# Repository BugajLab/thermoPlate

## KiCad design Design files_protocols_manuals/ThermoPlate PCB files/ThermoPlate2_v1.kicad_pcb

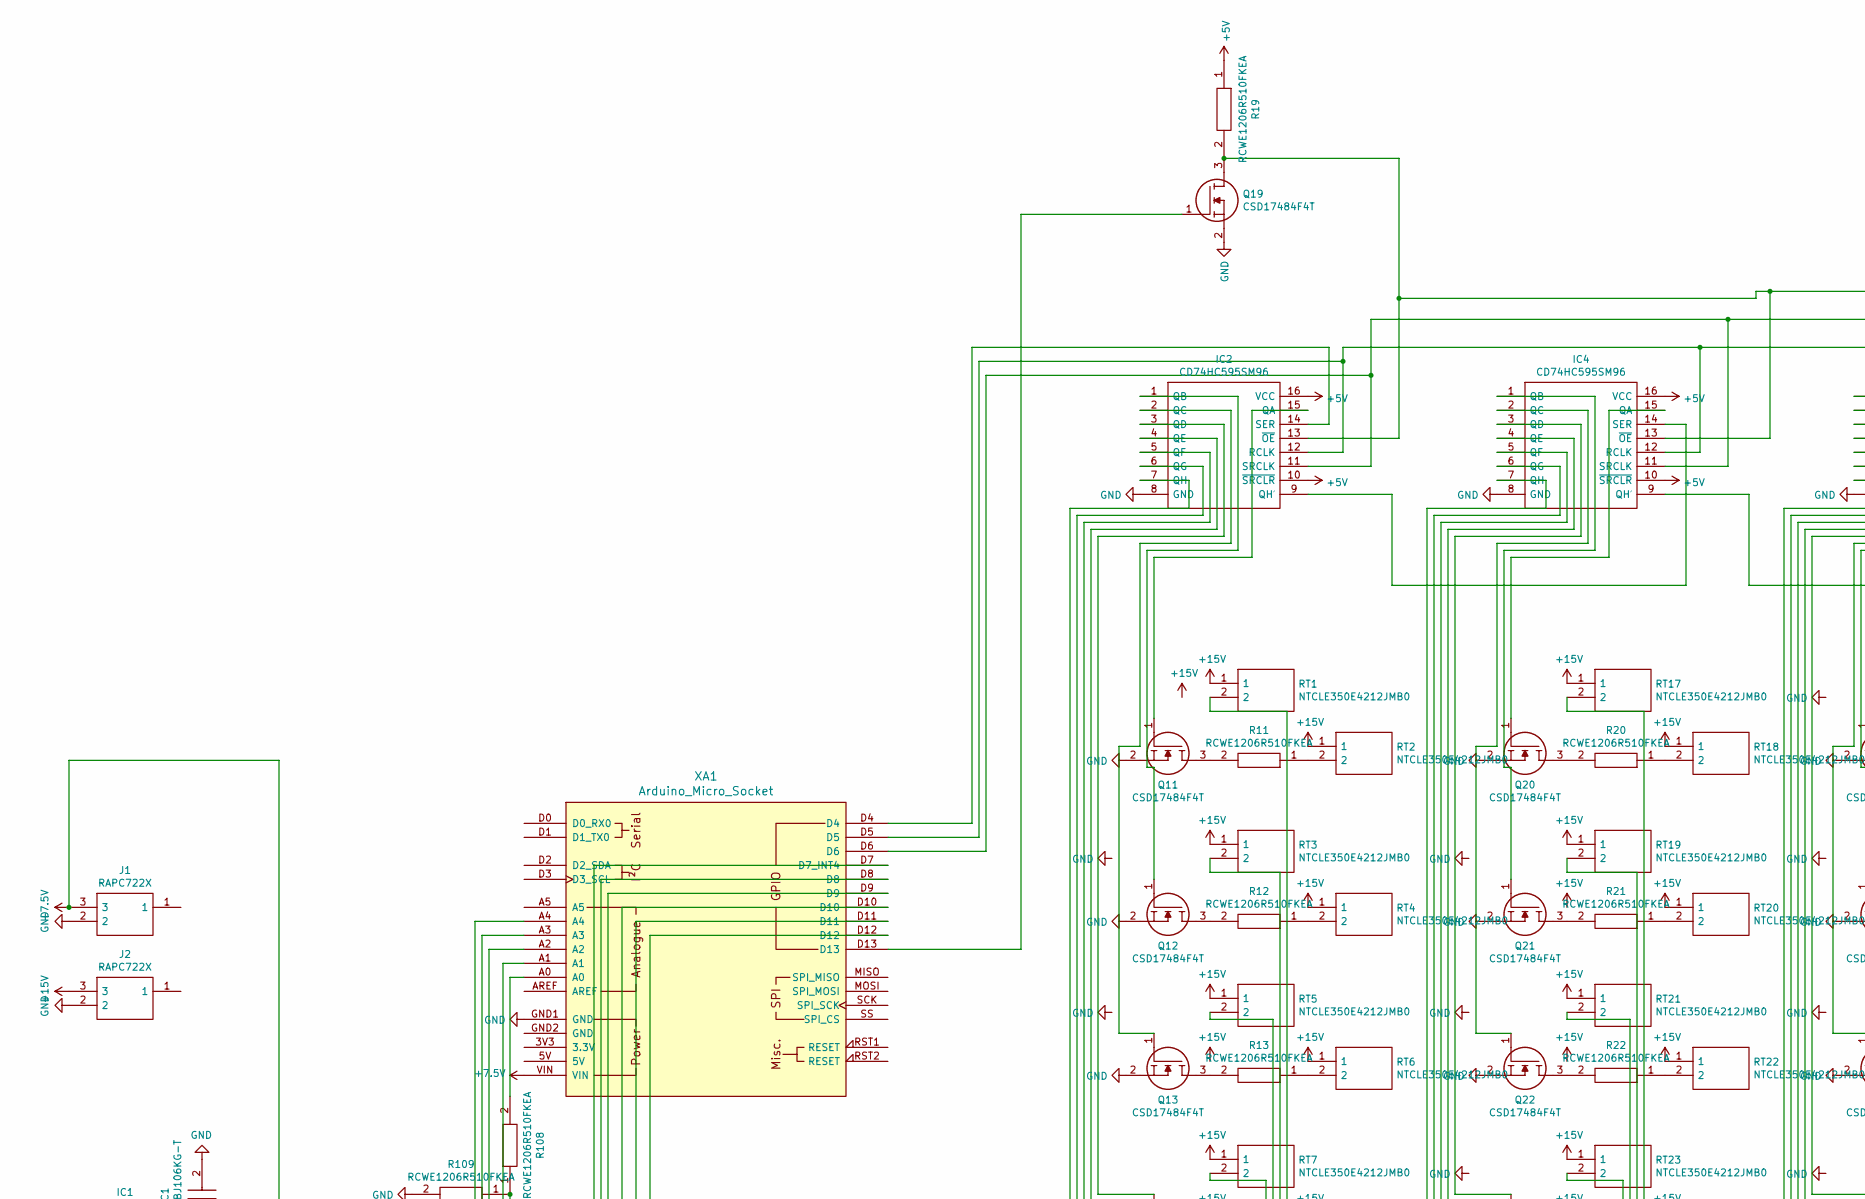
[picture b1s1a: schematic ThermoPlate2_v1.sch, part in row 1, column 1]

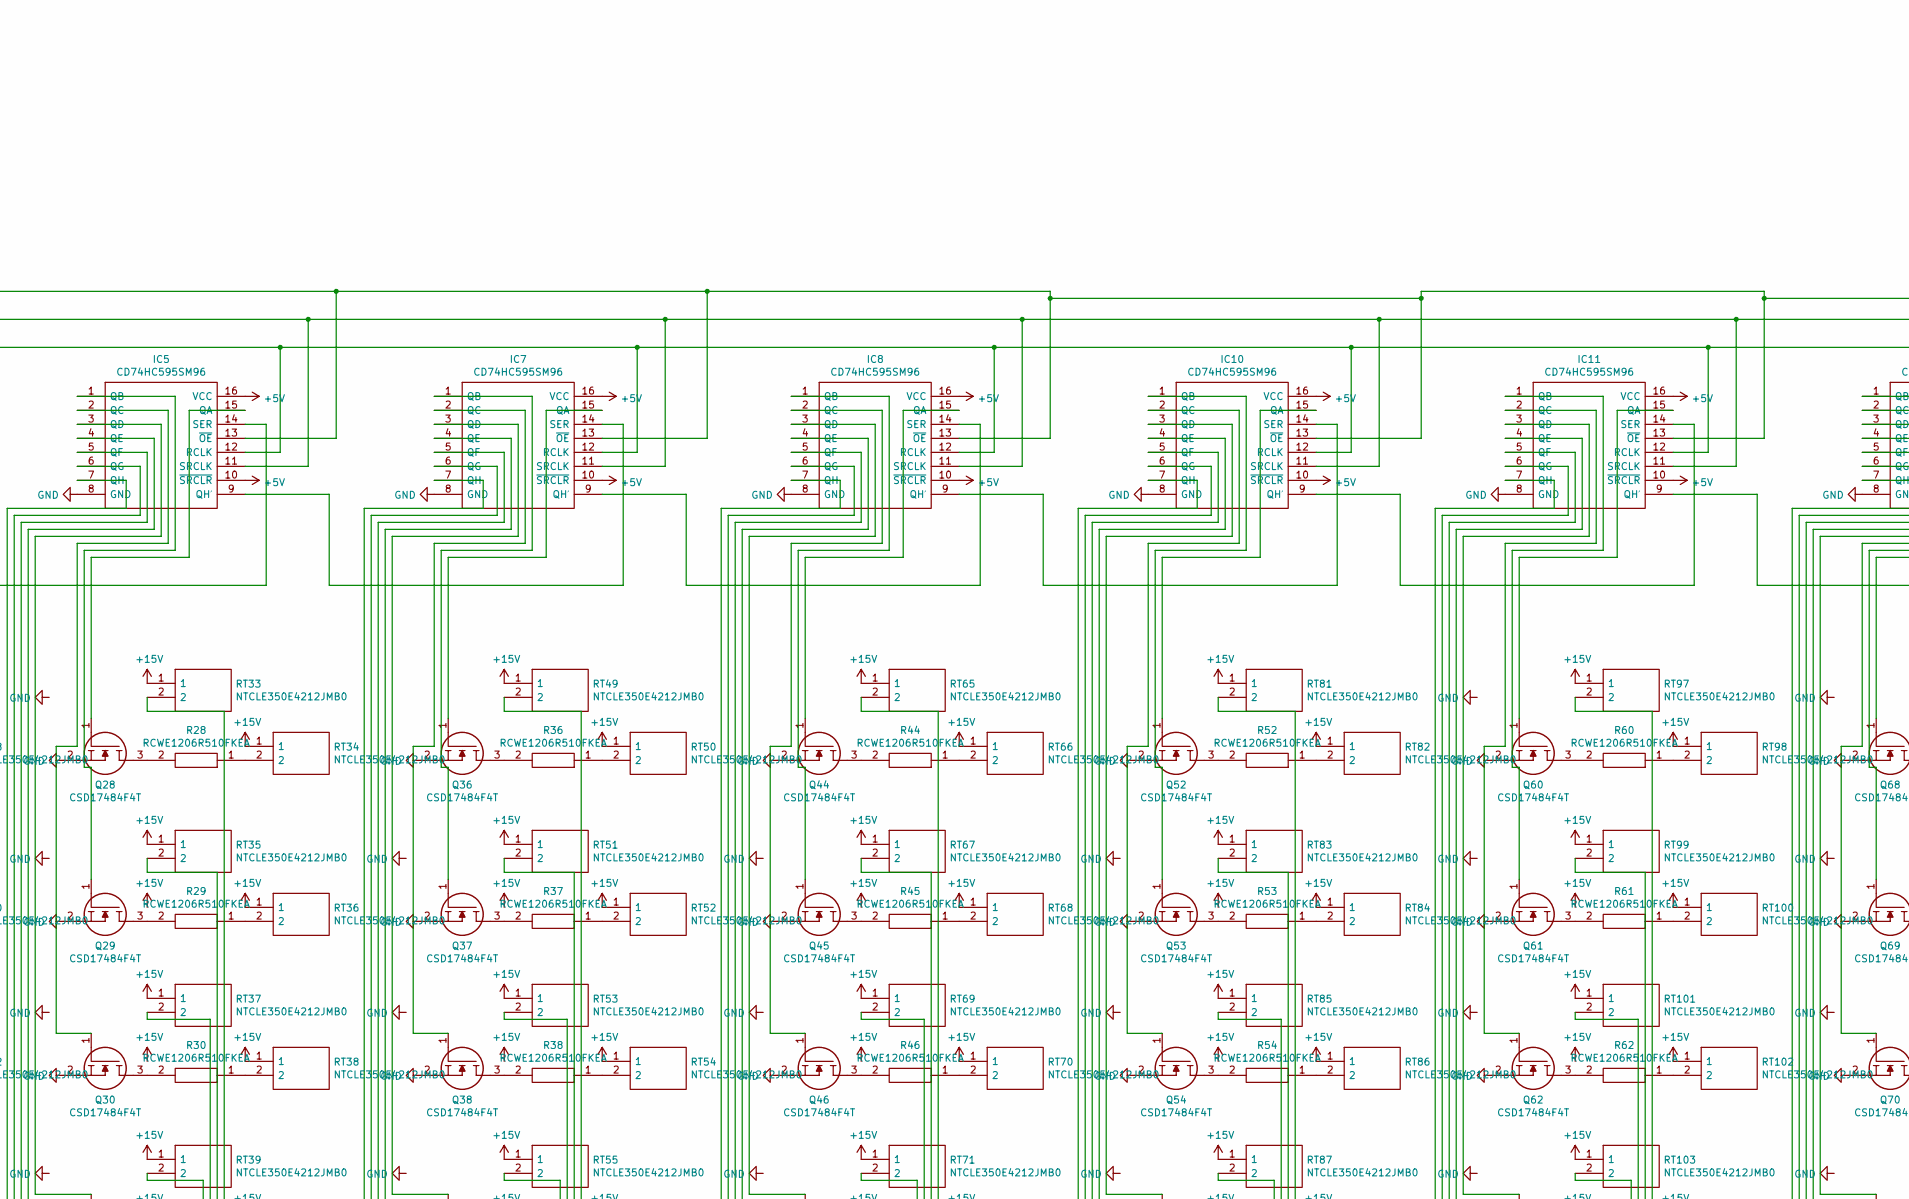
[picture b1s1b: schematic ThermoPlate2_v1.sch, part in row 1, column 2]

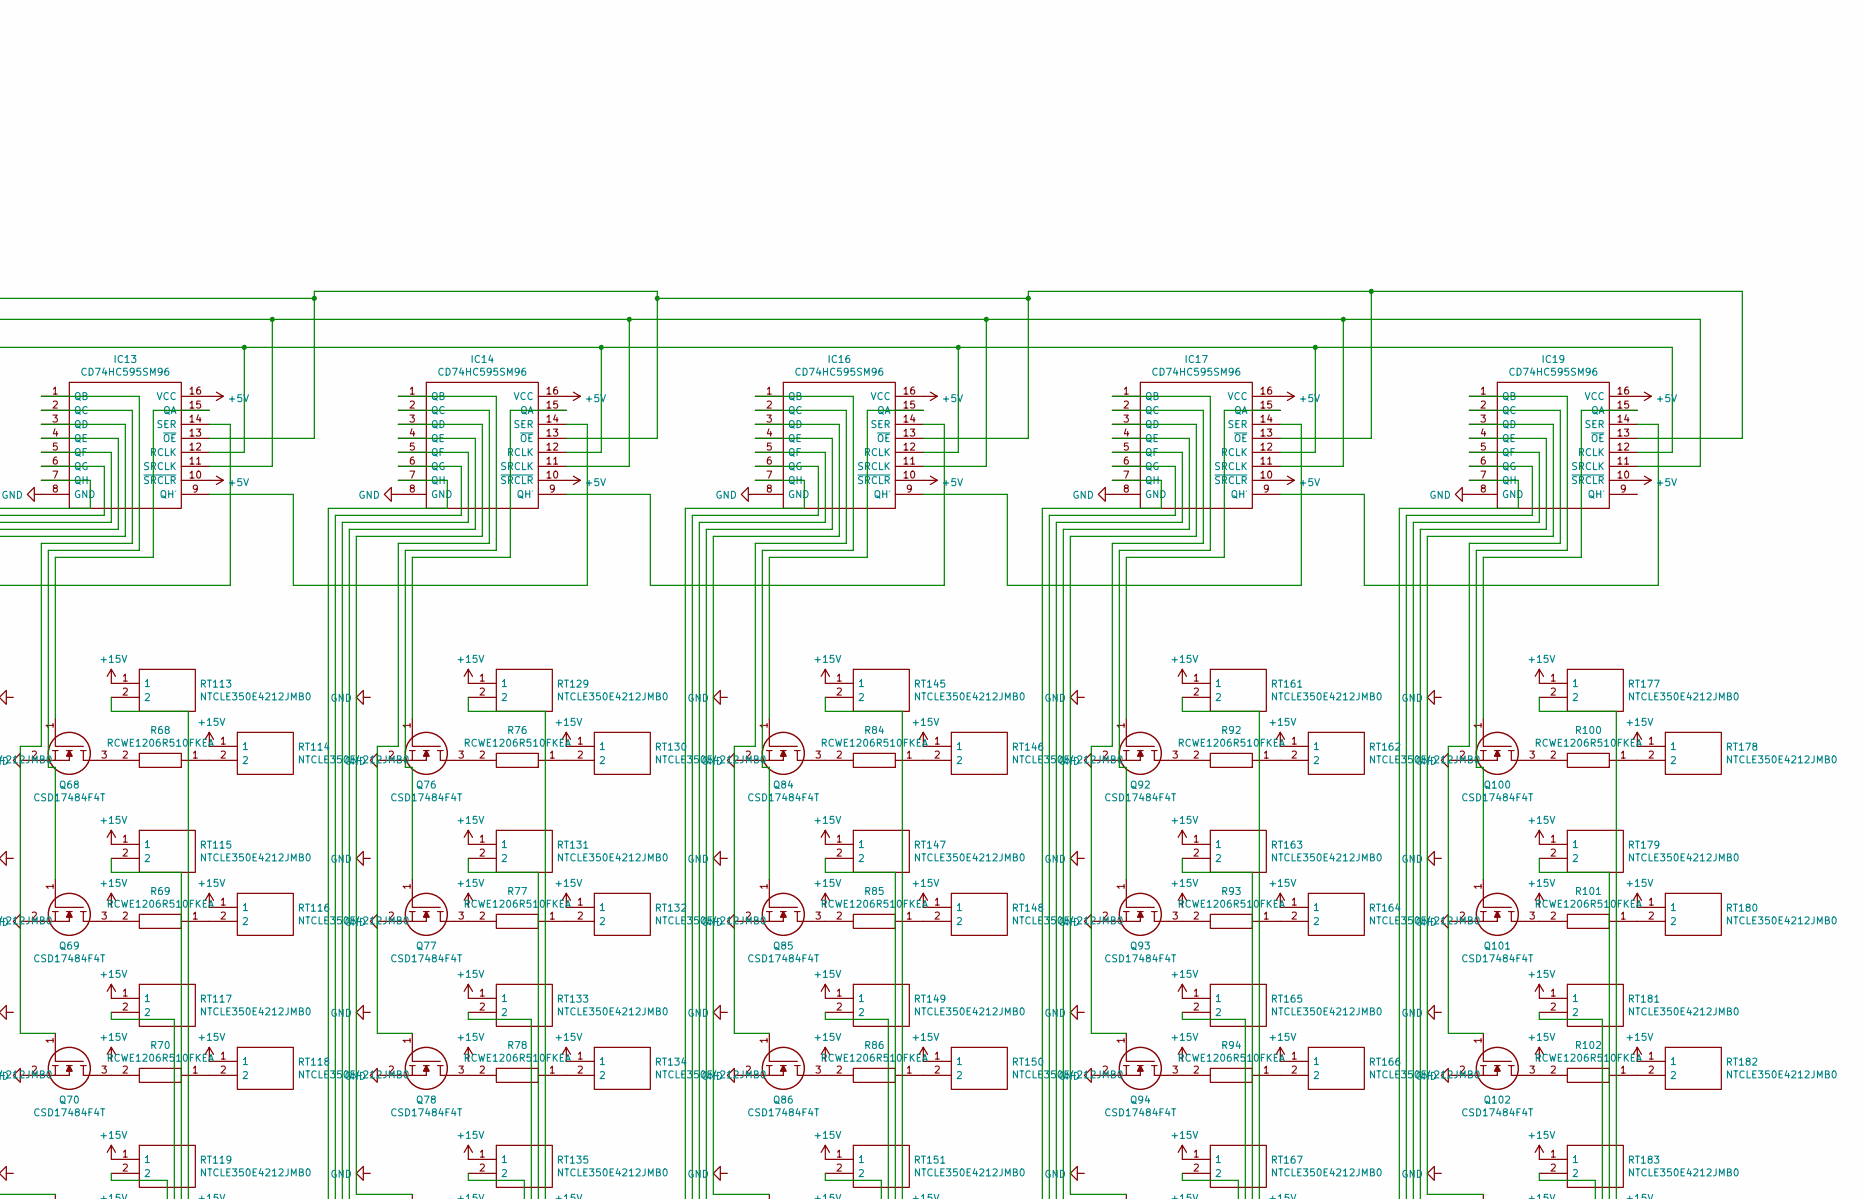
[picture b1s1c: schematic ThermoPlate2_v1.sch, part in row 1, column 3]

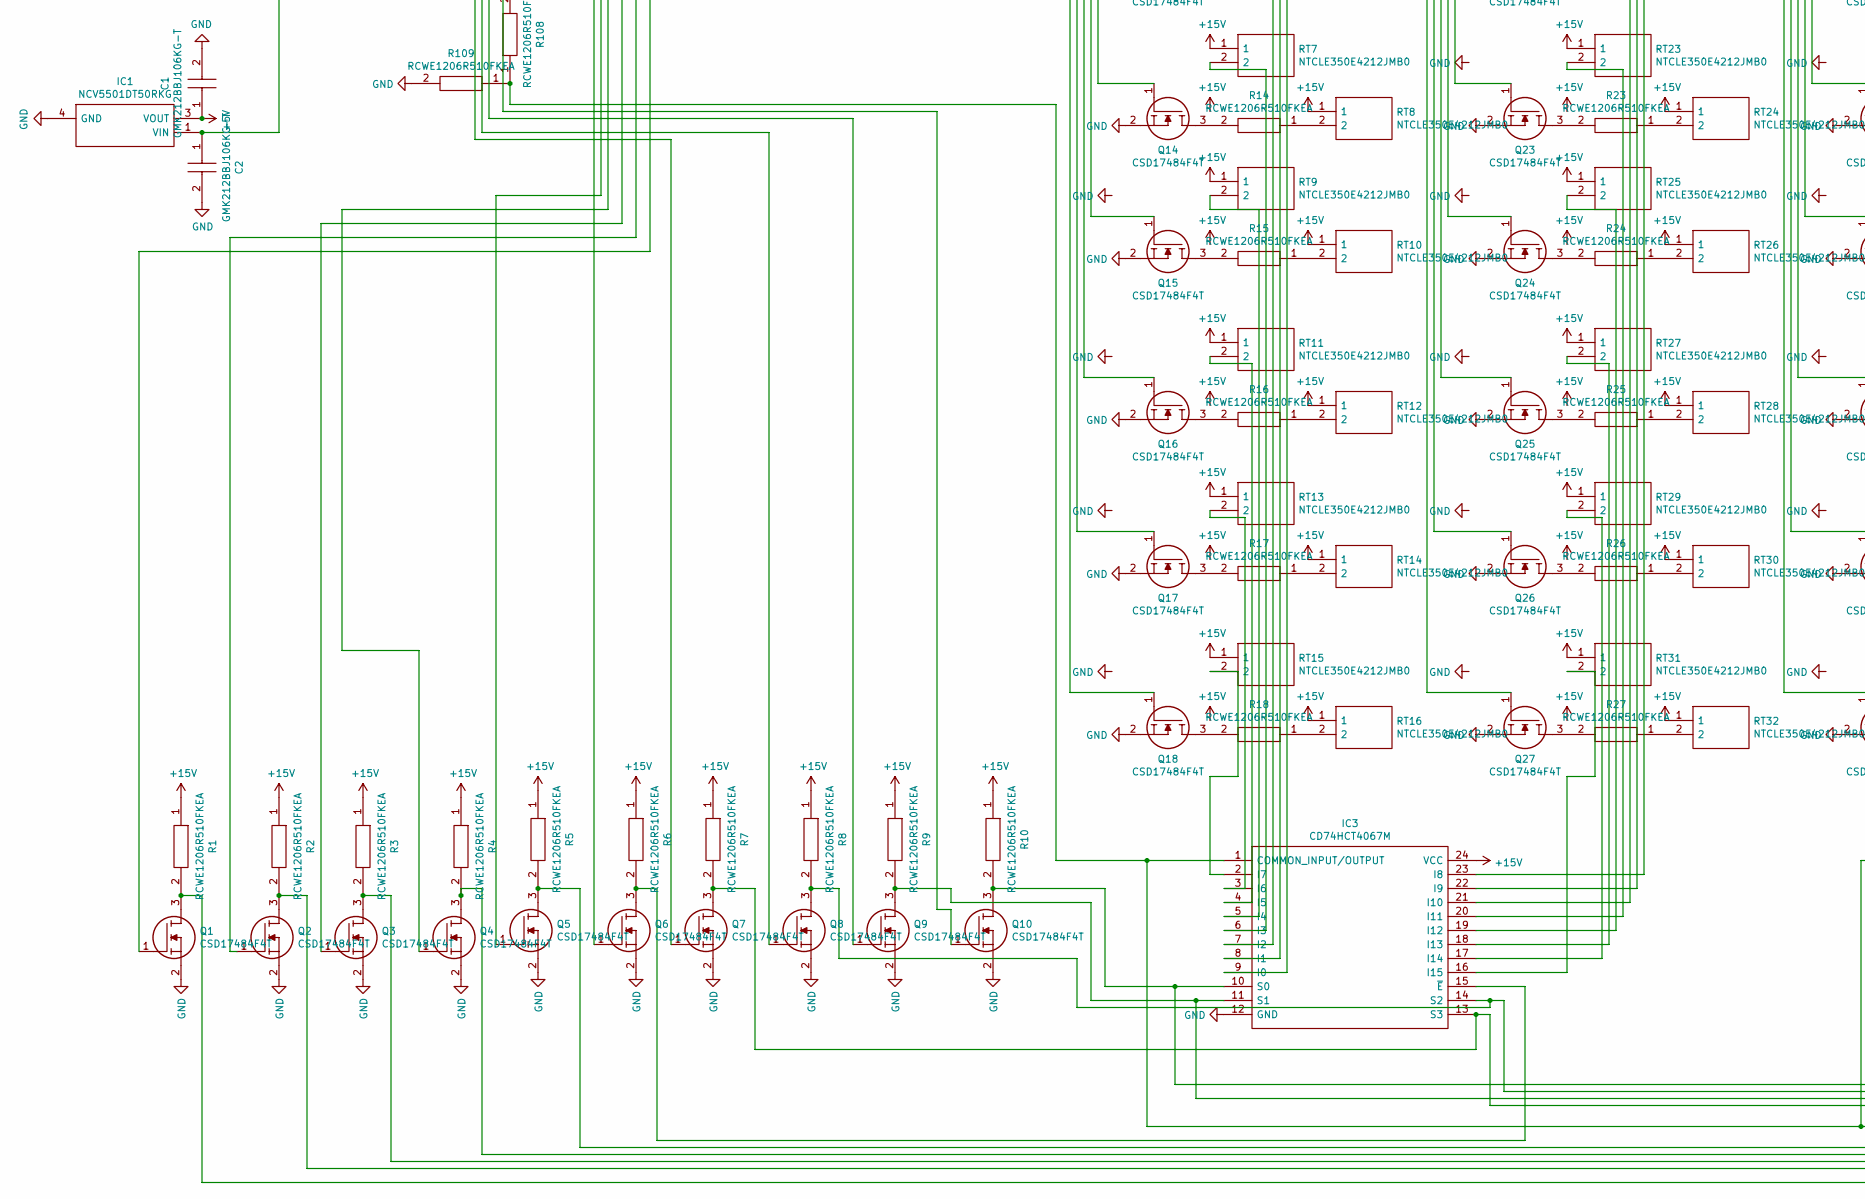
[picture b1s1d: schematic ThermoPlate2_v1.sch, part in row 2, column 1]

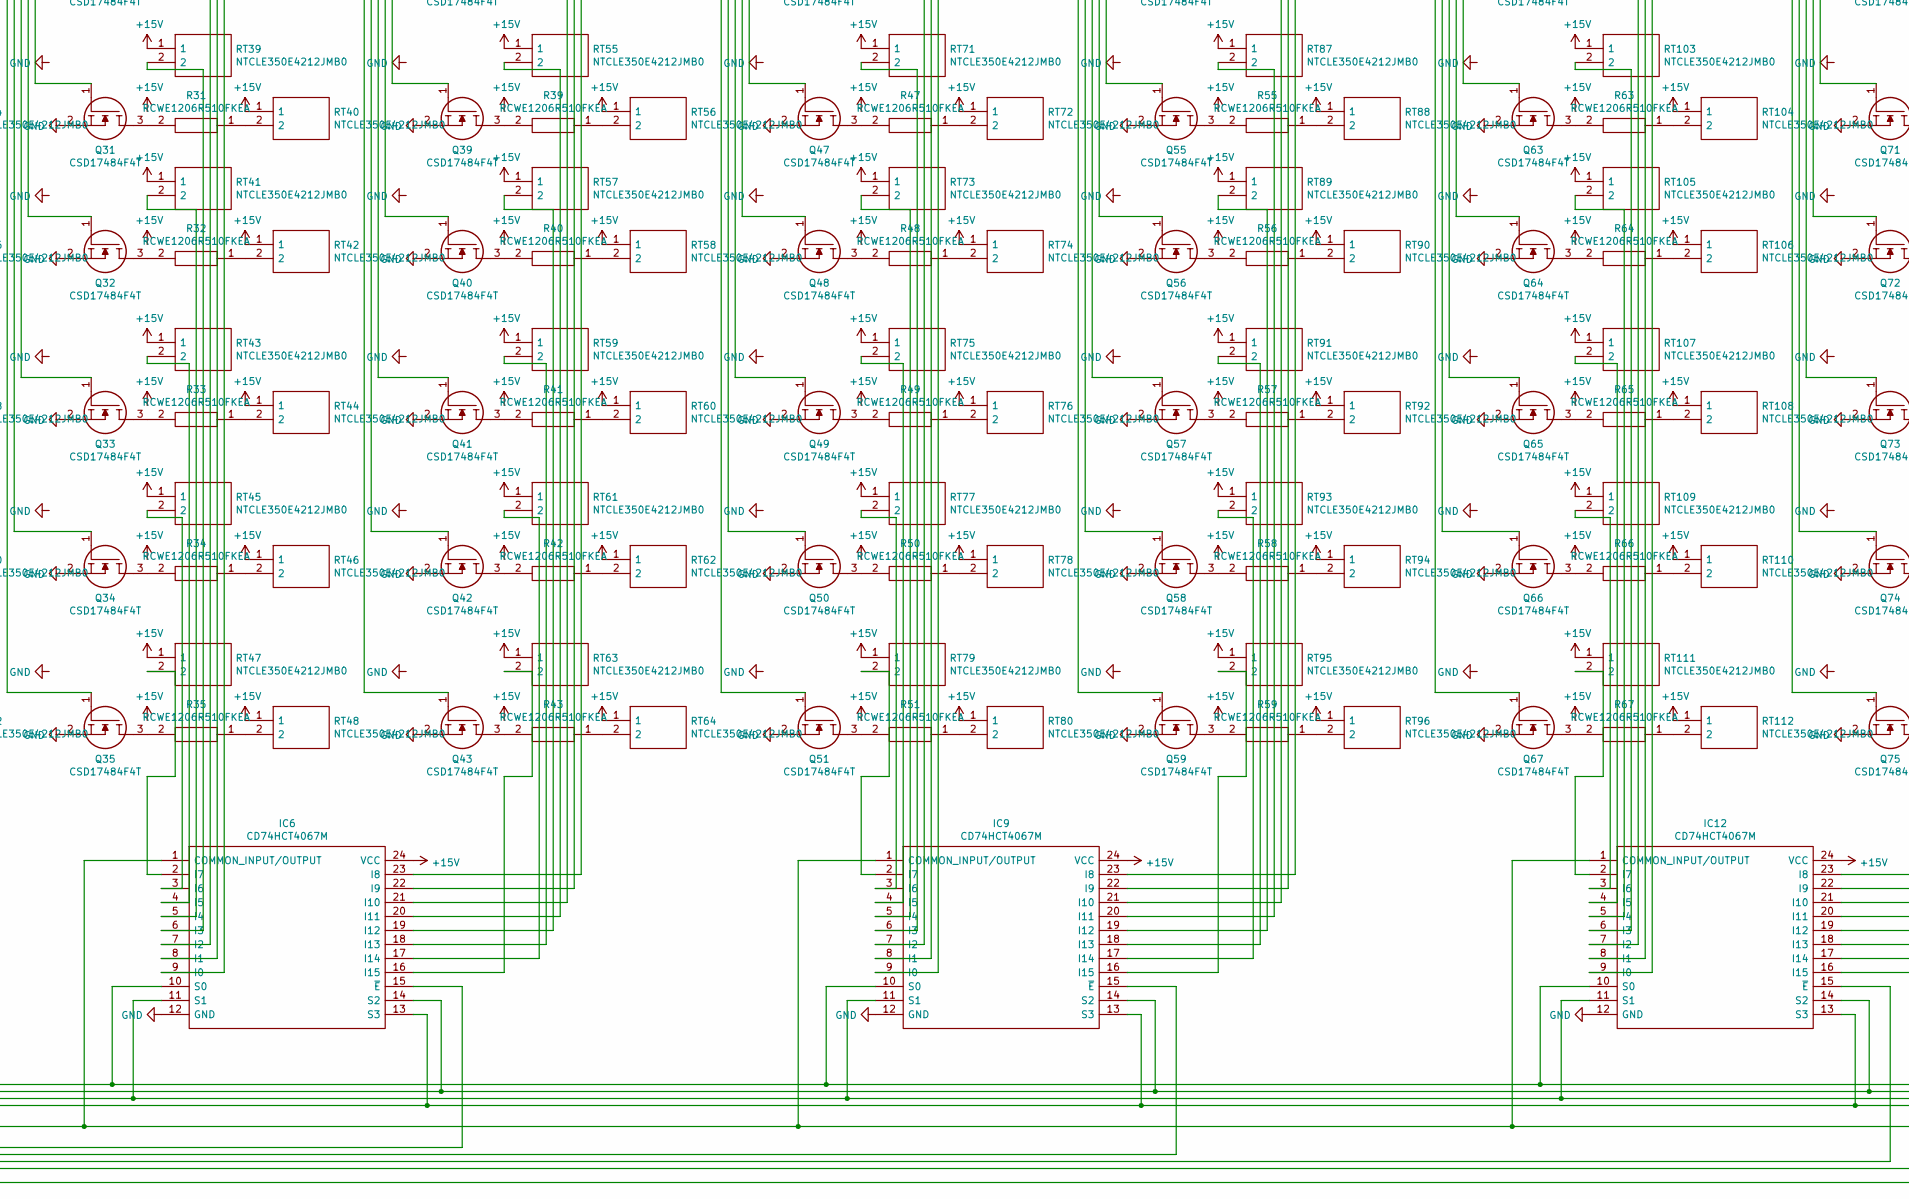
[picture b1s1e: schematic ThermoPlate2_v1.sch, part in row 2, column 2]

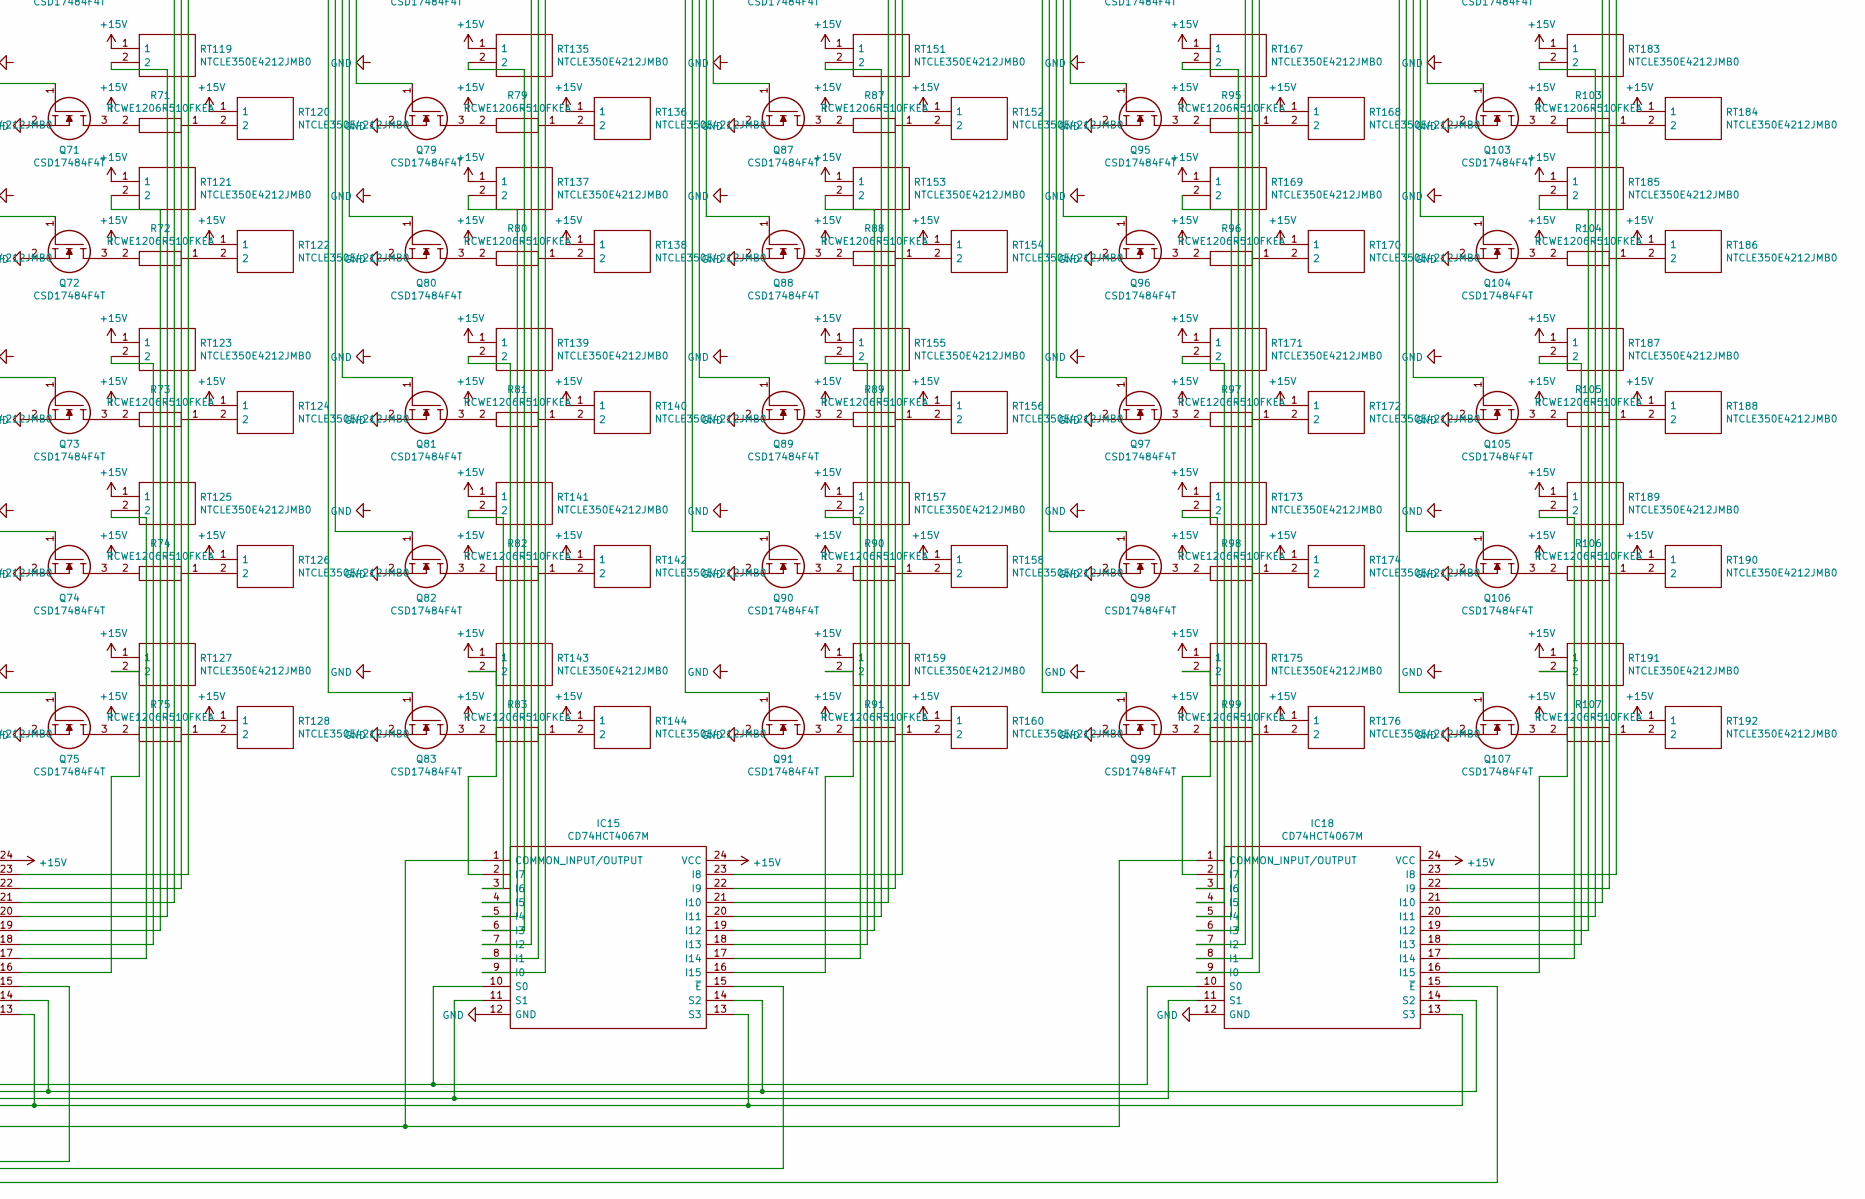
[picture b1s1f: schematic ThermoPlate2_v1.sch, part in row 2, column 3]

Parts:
C1, C2: GMK212BBJ106KG-T; CAPC2012X135N; Mouser Part Number 963-GMK212BBJ106KG-T
IC1: NCV5501DT50RKG; Mouser Part Number 863-NCV5501DT50RKG
IC2, IC4, IC5, IC7, IC8, IC10, IC11, IC13, IC14, IC16, IC17, IC19: CD74HC595SM96; SOP65P780X200-16N; Mouser Part Number 595-CD74HC595SM96
IC3, IC6, IC9, IC12, IC15, IC18: CD74HCT4067M; SOIC127P1030X265-24N; Mouser Part Number 595-CD74HCT4067M
J1, J2: RAPC722X; Mouser Part Number 502-RAPC722X
Q1, Q2, Q3, Q4, Q5, Q6, Q7, Q8, Q9, Q10, Q11, Q12, Q13, Q14, Q15, Q16, Q17, Q18, Q19, Q20, Q21, Q22, Q23, Q24, Q25, Q26, Q27, Q28, Q29, Q30, Q31, Q32, Q33, Q34, Q35, Q36, Q37, Q38, Q39, Q40, Q41, Q42, Q43, Q44, Q45, Q46, Q47, Q48, Q49, Q50, Q51, Q52, Q53, Q54, Q55, Q56, Q57, Q58, Q59, Q60, Q61, Q62, Q63, Q64, Q65, Q66, Q67, Q68, Q69, Q70, Q71, Q72, Q73, Q74, Q75, Q76, Q77, Q78, Q79, Q80, Q81, Q82, Q83, Q84, Q85, Q86, Q87, Q88, Q89, Q90, Q91, Q92, Q93, Q94, Q95, Q96, Q97, Q98, Q99, Q100, Q101, Q102, Q103, Q104, Q105, Q106, Q107: CSD17484F4T; SOT95P230X110-3N; Mouser Part Number 595-CSD17484F4T
R1, R2, R3, R4, R5, R6, R7, R8, R9, R10, R11, R12, R13, R14, R15, R16, R17, R18, R19, R20, R21, R22, R23, R24, R25, R26, R27, R28, R29, R30, R31, R32, R33, R34, R35, R36, R37, R38, R39, R40, R41, R42, R43, R44, R45, R46, R47, R48, R49, R50, R51, R52, R53, R54, R55, R56, R57, R58, R59, R60, R61, R62, R63, R64, R65, R66, R67, R68, R69, R70, R71, R72, R73, R74, R75, R76, R77, R78, R79, R80, R81, R82, R83, R84, R85, R86, R87, R88, R89, R90, R91, R92, R93, R94, R95, R96, R97, R98, R99, R100, R101, R102, R103, R104, R105, R106, R107, R108, R109: RCWE1206R510FKEA; RESC3216X71N; Mouser Part Number 71-RCWE1206R510FKEA
RT1, RT2, RT3, RT4, RT5, RT6, RT7, RT8, RT9, RT10, RT11, RT12, RT13, RT14, RT15, RT16, RT17, RT18, RT19, RT20, RT21, RT22, RT23, RT24, RT25, RT26, RT27, RT28, RT29, RT30, RT31, RT32, RT33, RT34, RT35, RT36, RT37, RT38, RT39, RT40, RT41, RT42, RT43, RT44, RT45, RT46, RT47, RT48, RT49, RT50, RT51, RT52, RT53, RT54, RT55, RT56, RT57, RT58, RT59, RT60, RT61, RT62, RT63, RT64, RT65, RT66, RT67, RT68, RT69, RT70, RT71, RT72, RT73, RT74, RT75, RT76, RT77, RT78, RT79, RT80, RT81, RT82, RT83, RT84, RT85, RT86, RT87, RT88, RT89, RT90, RT91, RT92, RT93, RT94, RT95, RT96, RT97, RT98, RT99, RT100, RT101, RT102, RT103, RT104, RT105, RT106, RT107, RT108, RT109, RT110, RT111, RT112, RT113, RT114, RT115, RT116, RT117, RT118, RT119, RT120, RT121, RT122, RT123, RT124, RT125, RT126, RT127, RT128, RT129, RT130, RT131, RT132, RT133, RT134, RT135, RT136, RT137, RT138, RT139, RT140, RT141, RT142, RT143, RT144, RT145, RT146, RT147, RT148, RT149, RT150, RT151, RT152, RT153, RT154, RT155, RT156, RT157, RT158, RT159, RT160, RT161, RT162, RT163, RT164, RT165, RT166, RT167, RT168, RT169, RT170, RT171, RT172, RT173, RT174, RT175, RT176, RT177, RT178, RT179, RT180, RT181, RT182, RT183, RT184, RT185, RT186, RT187, RT188, RT189, RT190, RT191, RT192: NTCLE350E4212JMB0; NTCLE350E4103FHB0; Mouser Part Number 594-NTCLE350E4212JMB
XA1: Arduino_Micro_Socket

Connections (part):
+5V: C1.1, IC1.3 (VOUT), IC2.10 (~SRCLR), IC2.16 (VCC), IC4.10 (~SRCLR), IC4.16 (VCC), IC5.10 (~SRCLR), IC5.16 (VCC), IC7.10 (~SRCLR), IC7.16 (VCC), IC8.10 (~SRCLR), IC8.16 (VCC), IC10.10 (~SRCLR), IC10.16 (VCC), IC11.10 (~SRCLR), IC11.16 (VCC), IC13.10 (~SRCLR), IC13.16 (VCC), IC14.10 (~SRCLR), IC14.16 (VCC), IC16.10 (~SRCLR), IC16.16 (VCC), IC17.10 (~SRCLR), IC17.16 (VCC), IC19.10 (~SRCLR), IC19.16 (VCC), R19.1
+7.5V: C2.1, IC1.1 (VIN), J1.3, XA1.VIN
+15V: IC3.24 (VCC), IC6.24 (VCC), IC9.24 (VCC), IC12.24 (VCC), IC15.24 (VCC), IC18.24 (VCC), J2.3, R1.1, R2.1, R3.1, R4.1, R5.1, R6.1, R7.1, R8.1, R9.1, R10.1, RT1.1, RT2.1, RT3.1, RT4.1, RT5.1, RT6.1, RT7.1, RT8.1, RT9.1, RT10.1, RT11.1, RT12.1, RT13.1, RT14.1, RT15.1, RT16.1, RT17.1, RT18.1, RT19.1, RT20.1, RT21.1, RT22.1, RT23.1, RT24.1, RT25.1, RT26.1, RT27.1, RT28.1, RT29.1, RT30.1, RT31.1, RT32.1, RT33.1, RT34.1, RT35.1, RT36.1, RT37.1, RT38.1, RT39.1, RT40.1, RT41.1, RT42.1, RT43.1, RT44.1, RT45.1, RT46.1, RT47.1, RT48.1, RT49.1, RT50.1, RT51.1, RT52.1, RT53.1, RT54.1, RT55.1, RT56.1, RT57.1, RT58.1, RT59.1, RT60.1, RT61.1, RT62.1, RT63.1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
GND: C1.2, C2.2, IC1.4 (GND), IC2.8 (GND), IC3.12 (GND), IC4.8 (GND), IC5.8 (GND), IC6.12 (GND), IC7.8 (GND), IC8.8 (GND), IC9.12 (GND), IC10.8 (GND), IC11.8 (GND), IC12.12 (GND), IC13.8 (GND), IC14.8 (GND), IC15.12 (GND), IC16.8 (GND), IC17.8 (GND), IC18.12 (GND), IC19.8 (GND), J1.2, J2.2, Q1.2, Q2.2, Q3.2, Q4.2, Q5.2, Q6.2, Q7.2, Q8.2, Q9.2, Q10.2, Q11.2, Q12.2, Q13.2, Q14.2, Q15.2, Q16.2, Q17.2, Q18.2, Q19.2, Q20.2, Q21.2, Q22.2, Q23.2, Q24.2, Q25.2, Q26.2, Q27.2, Q28.2, Q29.2, Q30.2, Q31.2, Q32.2, Q33.2, Q34.2, Q35.2, Q36.2, Q37.2, Q38.2, Q39.2, Q40.2, Q41.2, Q42.2, Q43.2, Q44.2, Q45.2, Q46.2, Q47.2, Q48.2, Q49.2, Q50.2, Q51.2, Q52.2, Q53.2, Q54.2, Q55.2, Q56.2, Q57.2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
unnamed: IC2.1 (QB), Q12.1
unnamed: IC2.2 (QC), Q13.1
unnamed: IC2.3 (QD), Q14.1
unnamed: IC2.4 (QE), Q15.1
unnamed: IC2.5 (QF), Q16.1
unnamed: IC2.6 (QG), Q17.1
unnamed: IC2.7 (QH), Q18.1
unnamed: IC2.9 (QH′), IC4.14 (SER)
unnamed: IC2.14 (SER), XA1.D4
unnamed: IC2.15 (QA), Q11.1
unnamed: IC3.2 (I7), RT15.2
unnamed: IC3.3 (I6), RT13.2
unnamed: IC3.4 (I5), RT11.2
unnamed: IC3.5 (I4), RT9.2
unnamed: IC3.6 (I3), RT7.2
unnamed: IC3.7 (I2), RT5.2
unnamed: IC3.8 (I1), RT3.2
unnamed: IC3.9 (I0), RT1.2
unnamed: IC3.15 (~E), Q6.3, R6.2
unnamed: IC3.16 (I15), RT31.2
unnamed: IC3.17 (I14), RT29.2
unnamed: IC3.18 (I13), RT27.2
unnamed: IC3.19 (I12), RT25.2
unnamed: IC3.20 (I11), RT23.2
unnamed: IC3.21 (I10), RT21.2
unnamed: IC3.22 (I9), RT19.2
unnamed: IC3.23 (I8), RT17.2
unnamed: IC4.1 (QB), Q21.1
unnamed: IC4.2 (QC), Q22.1
unnamed: IC4.3 (QD), Q23.1
unnamed: IC4.4 (QE), Q24.1
unnamed: IC4.5 (QF), Q25.1
unnamed: IC4.6 (QG), Q26.1
unnamed: IC4.7 (QH), Q27.1
unnamed: IC4.9 (QH′), IC5.14 (SER)
unnamed: IC4.15 (QA), Q20.1
unnamed: IC5.1 (QB), Q29.1
unnamed: IC5.2 (QC), Q30.1
unnamed: IC5.3 (QD), Q31.1
unnamed: IC5.4 (QE), Q32.1
unnamed: IC5.5 (QF), Q33.1
unnamed: IC5.6 (QG), Q34.1
unnamed: IC5.7 (QH), Q35.1
unnamed: IC5.9 (QH′), IC7.14 (SER)
unnamed: IC5.15 (QA), Q28.1
unnamed: IC6.2 (I7), RT47.2
unnamed: IC6.3 (I6), RT45.2
unnamed: IC6.4 (I5), RT43.2
unnamed: IC6.5 (I4), RT41.2
unnamed: IC6.6 (I3), RT39.2
unnamed: IC6.7 (I2), RT37.2
unnamed: IC6.8 (I1), RT35.2
unnamed: IC6.9 (I0), RT33.2
unnamed: IC6.15 (~E), Q5.3, R5.2
unnamed: IC6.16 (I15), RT63.2
unnamed: IC6.17 (I14), RT61.2
unnamed: IC6.18 (I13), RT59.2
unnamed: IC6.19 (I12), RT57.2
unnamed: IC6.20 (I11), RT55.2
unnamed: IC6.21 (I10), RT53.2
unnamed: IC6.22 (I9), RT51.2
unnamed: IC6.23 (I8), RT49.2
unnamed: IC7.1 (QB), Q37.1
unnamed: IC7.2 (QC), Q38.1
unnamed: IC7.3 (QD), Q39.1
unnamed: IC7.4 (QE), Q40.1
unnamed: IC7.5 (QF), Q41.1
unnamed: IC7.6 (QG), Q42.1
unnamed: IC7.7 (QH), Q43.1
unnamed: IC7.9 (QH′), IC8.14 (SER)
unnamed: IC7.15 (QA), Q36.1
unnamed: IC8.1 (QB), Q45.1
unnamed: IC8.2 (QC), Q46.1
unnamed: IC8.3 (QD), Q47.1
unnamed: IC8.4 (QE), Q48.1
unnamed: IC8.5 (QF), Q49.1
unnamed: IC8.6 (QG), Q50.1
unnamed: IC8.7 (QH), Q51.1
unnamed: IC8.15 (QA), Q44.1
unnamed: IC9.2 (I7), RT79.2
unnamed: IC9.3 (I6), RT77.2
unnamed: IC9.4 (I5), RT75.2
unnamed: IC9.5 (I4), RT73.2
unnamed: IC9.6 (I3), RT71.2
unnamed: IC9.7 (I2), RT69.2
unnamed: IC9.8 (I1), RT67.2
unnamed: IC9.9 (I0), RT65.2
unnamed: IC9.15 (~E), Q4.3, R4.2
unnamed: IC9.16 (I15), RT95.2
unnamed: IC9.17 (I14), RT93.2
unnamed: IC9.18 (I13), RT91.2
unnamed: IC9.19 (I12), RT89.2
unnamed: IC9.20 (I11), RT87.2
unnamed: IC9.21 (I10), RT85.2
unnamed: IC9.22 (I9), RT83.2
unnamed: IC9.23 (I8), RT81.2
unnamed: IC10.1 (QB), Q53.1
unnamed: IC10.2 (QC), Q54.1
unnamed: IC10.3 (QD), Q55.1
unnamed: IC10.4 (QE), Q56.1
unnamed: IC10.5 (QF), Q57.1
unnamed: IC10.6 (QG), Q58.1
unnamed: IC10.7 (QH), Q59.1
unnamed: IC10.9 (QH′), IC11.14 (SER)
unnamed: IC2.11 (SRCLK), IC4.11 (SRCLK), IC5.11 (SRCLK), IC7.11 (SRCLK), IC8.11 (SRCLK), IC10.11 (SRCLK), IC11.11 (SRCLK), IC13.11 (SRCLK), IC14.11 (SRCLK), IC16.11 (SRCLK), IC17.11 (SRCLK), IC19.11 (SRCLK), XA1.D6
unnamed: IC2.12 (RCLK), IC4.12 (RCLK), IC5.12 (RCLK), IC7.12 (RCLK), IC8.12 (RCLK), IC10.12 (RCLK), IC11.12 (RCLK), IC13.12 (RCLK), IC14.12 (RCLK), IC16.12 (RCLK), IC17.12 (RCLK), IC19.12 (RCLK), XA1.D5
unnamed: IC2.13 (~OE), IC4.13 (~OE), IC5.13 (~OE), IC7.13 (~OE), IC8.13 (~OE), IC10.13 (~OE), IC11.13 (~OE), IC13.13 (~OE), IC14.13 (~OE), IC16.13 (~OE), IC17.13 (~OE), IC19.13 (~OE), Q19.3, R19.2
unnamed: IC8.9 (QH′), IC10.14 (SER)
unnamed: IC10.15 (QA), Q52.1
unnamed: IC11.1 (QB), Q61.1
unnamed: IC11.2 (QC), Q62.1
unnamed: IC11.3 (QD), Q63.1
unnamed: IC11.4 (QE), Q64.1
unnamed: IC11.5 (QF), Q65.1
unnamed: IC11.6 (QG), Q66.1
unnamed: IC11.7 (QH), Q67.1
unnamed: IC11.9 (QH′), IC13.14 (SER)
unnamed: IC11.15 (QA), Q60.1
unnamed: IC3.1 (COMMON_INPUT/OUTPUT), IC6.1 (COMMON_INPUT/OUTPUT), IC9.1 (COMMON_INPUT/OUTPUT), IC12.1 (COMMON_INPUT/OUTPUT), IC15.1 (COMMON_INPUT/OUTPUT), IC18.1 (COMMON_INPUT/OUTPUT), R108.1, R109.1
unnamed: IC12.2 (I7), RT111.2
unnamed: IC12.3 (I6), RT109.2
unnamed: IC12.4 (I5), RT107.2
unnamed: IC12.5 (I4), RT105.2
unnamed: IC12.6 (I3), RT103.2
unnamed: IC12.7 (I2), RT101.2
unnamed: IC12.8 (I1), RT99.2
unnamed: IC12.9 (I0), RT97.2
unnamed: IC3.10 (S0), IC6.10 (S0), IC9.10 (S0), IC12.10 (S0), IC15.10 (S0), IC18.10 (S0), Q10.3, R10.2
unnamed: IC3.11 (S1), IC6.11 (S1), IC9.11 (S1), IC12.11 (S1), IC15.11 (S1), IC18.11 (S1), Q9.3, R9.2
unnamed: IC3.13 (S3), IC6.13 (S3), IC9.13 (S3), IC12.13 (S3), IC15.13 (S3), IC18.13 (S3), Q7.3, R7.2
unnamed: IC3.14 (S2), IC6.14 (S2), IC9.14 (S2), IC12.14 (S2), IC15.14 (S2), IC18.14 (S2), Q8.3, R8.2
unnamed: IC12.15 (~E), Q3.3, R3.2
unnamed: IC12.16 (I15), RT127.2
unnamed: IC12.17 (I14), RT125.2
unnamed: IC12.18 (I13), RT123.2
unnamed: IC12.19 (I12), RT121.2
unnamed: IC12.20 (I11), RT119.2
unnamed: IC12.21 (I10), RT117.2
unnamed: IC12.22 (I9), RT115.2
unnamed: IC12.23 (I8), RT113.2
unnamed: IC13.1 (QB), Q69.1
unnamed: IC13.2 (QC), Q70.1
unnamed: IC13.3 (QD), Q71.1
unnamed: IC13.4 (QE), Q72.1
unnamed: IC13.5 (QF), Q73.1
unnamed: IC13.6 (QG), Q74.1
unnamed: IC13.7 (QH), Q75.1
unnamed: IC13.9 (QH′), IC14.14 (SER)
unnamed: IC13.15 (QA), Q68.1
unnamed: IC14.1 (QB), Q77.1
unnamed: IC14.2 (QC), Q78.1
unnamed: IC14.3 (QD), Q79.1
unnamed: IC14.4 (QE), Q80.1
unnamed: IC14.5 (QF), Q81.1
unnamed: IC14.6 (QG), Q82.1
unnamed: IC14.7 (QH), Q83.1
unnamed: IC14.9 (QH′), IC16.14 (SER)
unnamed: IC14.15 (QA), Q76.1
unnamed: IC15.2 (I7), RT143.2
unnamed: IC15.3 (I6), RT141.2
unnamed: IC15.4 (I5), RT139.2
unnamed: IC15.5 (I4), RT137.2
unnamed: IC15.6 (I3), RT135.2
unnamed: IC15.7 (I2), RT133.2
unnamed: IC15.8 (I1), RT131.2
unnamed: IC15.9 (I0), RT129.2
unnamed: IC15.15 (~E), Q2.3, R2.2
unnamed: IC15.16 (I15), RT159.2
unnamed: IC15.17 (I14), RT157.2
unnamed: IC15.18 (I13), RT155.2
unnamed: IC15.19 (I12), RT153.2
unnamed: IC15.20 (I11), RT151.2
unnamed: IC15.21 (I10), RT149.2
unnamed: IC15.22 (I9), RT147.2
unnamed: IC15.23 (I8), RT145.2
unnamed: IC16.1 (QB), Q85.1
unnamed: IC16.2 (QC), Q86.1
unnamed: IC16.3 (QD), Q87.1
unnamed: IC16.4 (QE), Q88.1
unnamed: IC16.5 (QF), Q89.1
unnamed: IC16.6 (QG), Q90.1
unnamed: IC16.7 (QH), Q91.1
unnamed: IC16.9 (QH′), IC17.14 (SER)
unnamed: IC16.15 (QA), Q84.1
unnamed: IC17.1 (QB), Q93.1
unnamed: IC17.2 (QC), Q94.1
unnamed: IC17.3 (QD), Q95.1
unnamed: IC17.4 (QE), Q96.1
unnamed: IC17.5 (QF), Q97.1
unnamed: IC17.6 (QG), Q98.1
unnamed: IC17.7 (QH), Q99.1
unnamed: IC17.9 (QH′), IC19.14 (SER)
unnamed: IC17.15 (QA), Q92.1
unnamed: IC18.2 (I7), RT175.2
unnamed: IC18.3 (I6), RT173.2
unnamed: IC18.4 (I5), RT171.2
unnamed: IC18.5 (I4), RT169.2
unnamed: IC18.6 (I3), RT167.2
unnamed: IC18.7 (I2), RT165.2
unnamed: IC18.8 (I1), RT163.2
unnamed: IC18.9 (I0), RT161.2
unnamed: IC18.15 (~E), Q1.3, R1.2
unnamed: IC18.16 (I15), RT191.2
unnamed: IC18.17 (I14), RT189.2
unnamed: IC18.18 (I13), RT187.2
unnamed: IC18.19 (I12), RT185.2
unnamed: IC18.20 (I11), RT183.2
unnamed: IC18.21 (I10), RT181.2
unnamed: IC18.22 (I9), RT179.2
unnamed: IC18.23 (I8), RT177.2
unnamed: IC19.1 (QB), Q101.1
unnamed: IC19.2 (QC), Q102.1
unnamed: IC19.3 (QD), Q103.1
unnamed: IC19.4 (QE), Q104.1
unnamed: IC19.5 (QF), Q105.1
unnamed: IC19.6 (QG), Q106.1
unnamed: IC19.7 (QH), Q107.1
unnamed: IC19.15 (QA), Q100.1
unnamed: Q1.1, XA1.D12
unnamed: Q2.1, XA1.D11
unnamed: Q3.1, XA1.D10
unnamed: Q4.1, XA1.D9
unnamed: Q5.1, XA1.D8
unnamed: Q6.1, XA1.D7 (D7_INT4)
unnamed: Q7.1, XA1.A4
unnamed: Q8.1, XA1.A3
unnamed: Q9.1, XA1.A2
unnamed: Q10.1, XA1.A1
unnamed: Q11.3, R11.2
unnamed: Q12.3, R12.2
unnamed: Q13.3, R13.2
unnamed: Q14.3, R14.2
unnamed: Q15.3, R15.2
unnamed: Q16.3, R16.2
unnamed: Q17.3, R17.2
unnamed: Q18.3, R18.2
unnamed: Q19.1, XA1.D13
unnamed: Q20.3, R20.2
unnamed: Q21.3, R21.2
unnamed: Q22.3, R22.2
unnamed: Q23.3, R23.2
unnamed: Q24.3, R24.2
unnamed: Q25.3, R25.2
unnamed: Q26.3, R26.2
unnamed: Q27.3, R27.2
unnamed: Q28.3, R28.2
unnamed: Q29.3, R29.2
unnamed: Q30.3, R30.2
unnamed: Q31.3, R31.2
unnamed: Q32.3, R32.2
unnamed: Q33.3, R33.2
unnamed: Q34.3, R34.2
unnamed: Q35.3, R35.2
unnamed: Q36.3, R36.2
unnamed: Q37.3, R37.2
unnamed: Q38.3, R38.2
unnamed: Q39.3, R39.2
unnamed: Q40.3, R40.2
unnamed: Q41.3, R41.2
unnamed: Q42.3, R42.2
unnamed: Q43.3, R43.2
unnamed: Q44.3, R44.2
unnamed: Q45.3, R45.2
unnamed: Q46.3, R46.2
unnamed: Q47.3, R47.2
unnamed: Q48.3, R48.2
unnamed: Q49.3, R49.2
unnamed: Q50.3, R50.2
unnamed: Q51.3, R51.2
unnamed: Q52.3, R52.2
unnamed: Q53.3, R53.2
unnamed: Q54.3, R54.2
unnamed: Q55.3, R55.2
unnamed: Q56.3, R56.2
unnamed: Q57.3, R57.2
unnamed: Q58.3, R58.2
unnamed: Q59.3, R59.2
unnamed: Q60.3, R60.2
unnamed: Q61.3, R61.2
unnamed: Q62.3, R62.2
unnamed: Q63.3, R63.2
unnamed: Q64.3, R64.2
unnamed: Q65.3, R65.2
unnamed: Q66.3, R66.2
unnamed: Q67.3, R67.2
unnamed: Q68.3, R68.2
unnamed: Q69.3, R69.2
unnamed: Q70.3, R70.2
unnamed: Q71.3, R71.2
unnamed: Q72.3, R72.2
unnamed: Q73.3, R73.2
unnamed: Q74.3, R74.2
unnamed: Q75.3, R75.2
unnamed: Q76.3, R76.2
unnamed: Q77.3, R77.2
unnamed: Q78.3, R78.2
unnamed: Q79.3, R79.2
unnamed: Q80.3, R80.2
unnamed: Q81.3, R81.2
unnamed: Q82.3, R82.2
unnamed: Q83.3, R83.2
unnamed: Q84.3, R84.2
unnamed: Q85.3, R85.2
unnamed: Q86.3, R86.2
unnamed: Q87.3, R87.2
unnamed: Q88.3, R88.2
unnamed: Q89.3, R89.2
unnamed: Q90.3, R90.2
unnamed: Q91.3, R91.2
unnamed: Q92.3, R92.2
unnamed: Q93.3, R93.2
unnamed: Q94.3, R94.2
unnamed: Q95.3, R95.2
unnamed: Q96.3, R96.2
unnamed: Q97.3, R97.2
unnamed: Q98.3, R98.2
unnamed: Q99.3, R99.2
unnamed: Q100.3, R100.2
unnamed: Q101.3, R101.2
unnamed: Q102.3, R102.2
unnamed: Q103.3, R103.2
unnamed: Q104.3, R104.2
unnamed: Q105.3, R105.2
unnamed: Q106.3, R106.2
unnamed: Q107.3, R107.2
unnamed: R11.1, RT2.2
unnamed: R12.1, RT4.2
unnamed: R13.1, RT6.2
unnamed: R14.1, RT8.2
unnamed: R15.1, RT10.2
unnamed: R16.1, RT12.2
unnamed: R17.1, RT14.2
unnamed: R18.1, RT16.2
unnamed: R20.1, RT18.2
unnamed: R21.1, RT20.2
unnamed: R22.1, RT22.2
unnamed: R23.1, RT24.2
unnamed: R24.1, RT26.2
unnamed: R25.1, RT28.2
unnamed: R26.1, RT30.2
unnamed: R27.1, RT32.2
unnamed: R28.1, RT34.2
unnamed: R29.1, RT36.2
unnamed: R30.1, RT38.2
unnamed: R31.1, RT40.2
unnamed: R32.1, RT42.2
unnamed: R33.1, RT44.2
unnamed: R34.1, RT46.2
unnamed: R35.1, RT48.2
unnamed: R36.1, RT50.2
unnamed: R37.1, RT52.2
unnamed: R38.1, RT54.2
unnamed: R39.1, RT56.2
unnamed: R40.1, RT58.2
unnamed: R41.1, RT60.2
unnamed: R42.1, RT62.2
unnamed: R43.1, RT64.2
unnamed: R44.1, RT66.2
unnamed: R45.1, RT68.2
unnamed: R46.1, RT70.2
unnamed: R47.1, RT72.2
unnamed: R48.1, RT74.2
unnamed: R49.1, RT76.2
unnamed: R50.1, RT78.2
unnamed: R51.1, RT80.2
unnamed: R52.1, RT82.2
unnamed: R53.1, RT84.2
unnamed: R54.1, RT86.2
unnamed: R55.1, RT88.2
unnamed: R56.1, RT90.2
unnamed: R57.1, RT92.2
unnamed: R58.1, RT94.2
unnamed: R59.1, RT96.2
unnamed: R60.1, RT98.2
unnamed: R61.1, RT100.2
unnamed: R62.1, RT102.2
unnamed: R63.1, RT104.2
unnamed: R64.1, RT106.2
unnamed: R65.1, RT108.2
unnamed: R66.1, RT110.2
unnamed: R67.1, RT112.2
unnamed: R68.1, RT114.2
unnamed: R69.1, RT116.2
unnamed: R70.1, RT118.2
unnamed: R71.1, RT120.2
unnamed: R72.1, RT122.2
unnamed: R73.1, RT124.2
unnamed: R74.1, RT126.2
unnamed: R75.1, RT128.2
unnamed: R76.1, RT130.2
unnamed: R77.1, RT132.2
unnamed: R78.1, RT134.2
unnamed: R79.1, RT136.2
unnamed: R80.1, RT138.2
unnamed: R81.1, RT140.2
unnamed: R82.1, RT142.2
unnamed: R83.1, RT144.2
unnamed: R84.1, RT146.2
unnamed: R85.1, RT148.2
unnamed: R86.1, RT150.2
unnamed: R87.1, RT152.2
unnamed: R88.1, RT154.2
unnamed: R89.1, RT156.2
unnamed: R90.1, RT158.2
unnamed: R91.1, RT160.2
unnamed: R92.1, RT162.2
unnamed: R93.1, RT164.2
unnamed: R94.1, RT166.2
unnamed: R95.1, RT168.2
unnamed: R96.1, RT170.2
unnamed: R97.1, RT172.2
unnamed: R98.1, RT174.2
unnamed: R99.1, RT176.2
unnamed: R100.1, RT178.2
unnamed: R101.1, RT180.2
unnamed: R102.1, RT182.2
unnamed: R103.1, RT184.2
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
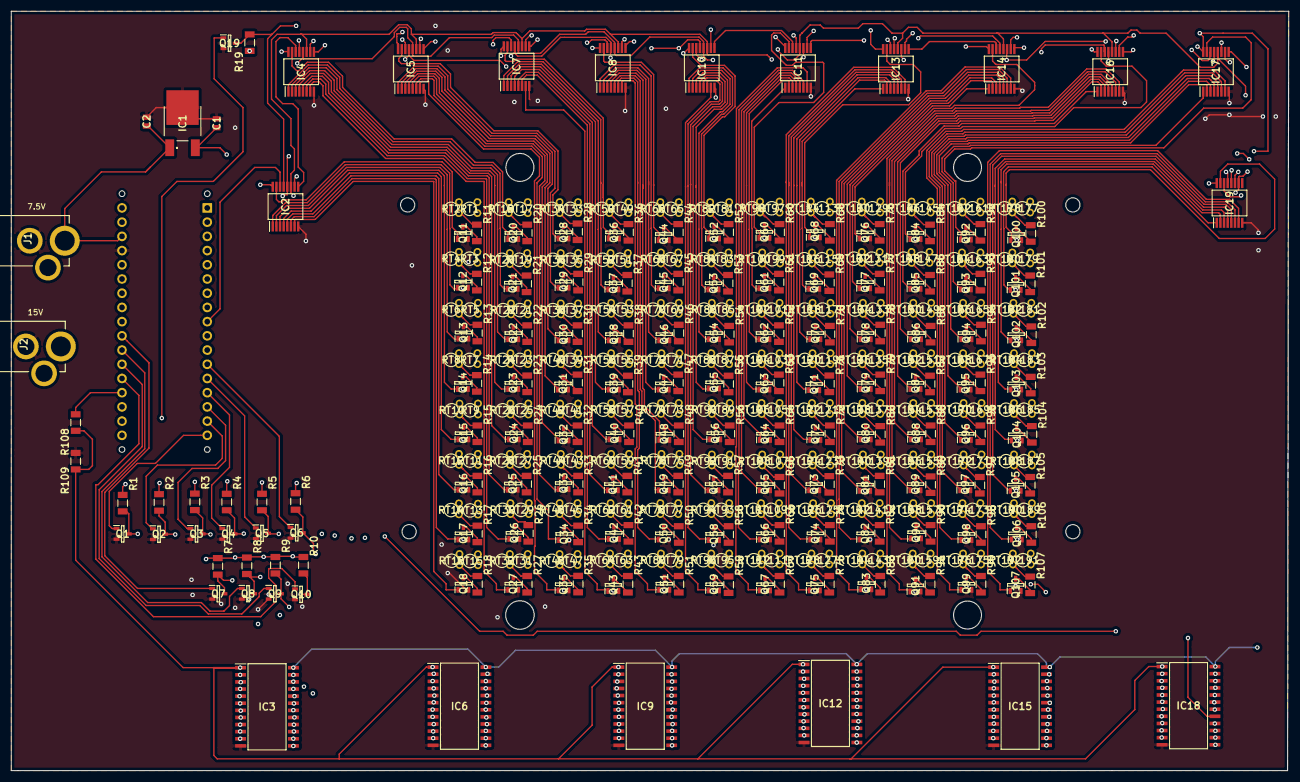
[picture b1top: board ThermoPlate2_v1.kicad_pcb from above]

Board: 4 copper layers, 228.3 x 135.7 mm, 432 parts (1 on the bottom side), 426 nets.

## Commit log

2024-12-09 Create LICENSE
2025-06-07 Add files via upload
    Fixed wrong part number for multiplexer
2025-06-07 Add files via upload
    fixed wrong multiplexer part number
